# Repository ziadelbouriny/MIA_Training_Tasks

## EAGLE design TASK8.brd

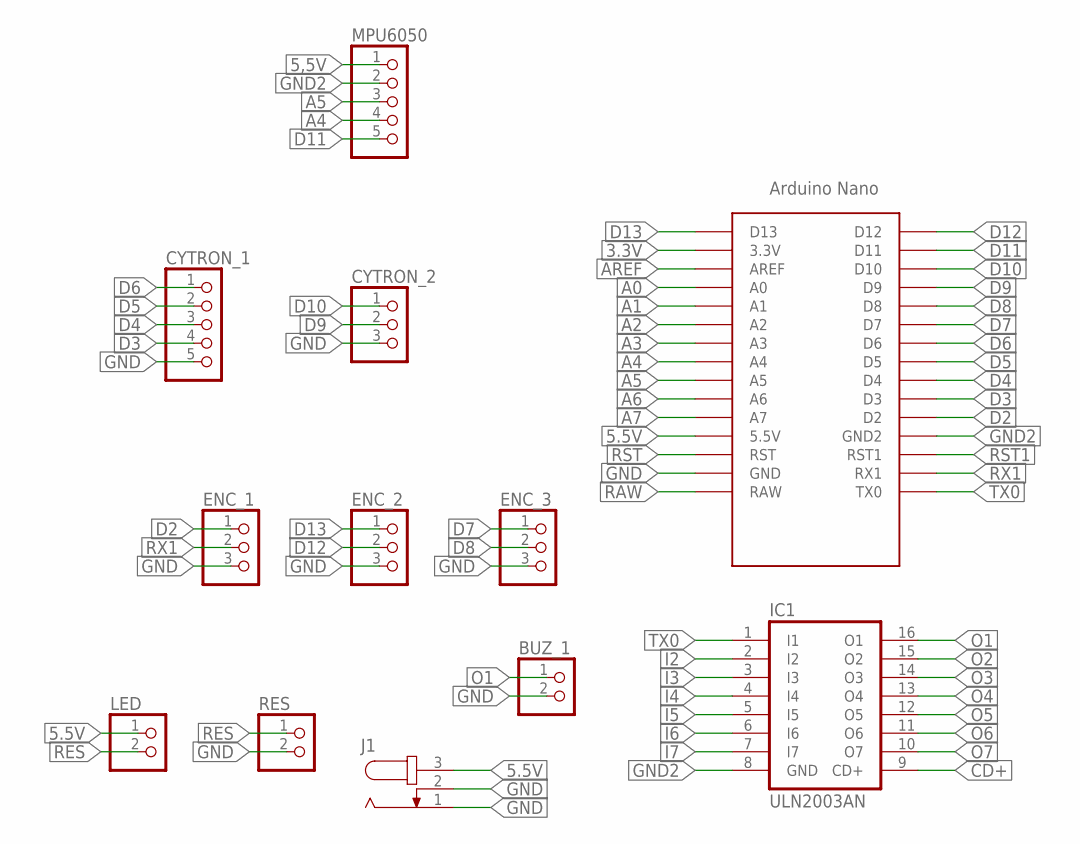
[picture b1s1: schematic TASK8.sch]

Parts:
BUZ_1: PINHD-1X2; 1X02
CYTRON_1: PINHD-1X5; 1X05
CYTRON_2: PINHD-1X3; 1X03
ENC_1, ENC_2, ENC_3: PINHD-1X3; 1X03
IC1: ULN2003AN; DIL16
J1: JACK-PLUG0; SPC4077
LED: PINHD-1X2; 1X02
MPU6050: PINHD-1X5; 1X05
RES: PINHD-1X2; 1X02
U$1: ARDUINO_NANO; NANO

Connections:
3.3V: U$1.3.3V
5,5V: MPU6050.1
5.5V: J1.3, LED.1, U$1.5V (5.5V)
A0: U$1.A0
A1: U$1.A1
A2: U$1.A2
A3: U$1.A3
A4: MPU6050.4, U$1.A4
A5: MPU6050.3, U$1.A5
A6: U$1.A6
A7: U$1.A7
AREF: U$1.AREF
CD+: IC1.9 (CD+)
D2: ENC_1.1, U$1.D2
D3: CYTRON_1.4, U$1.D3
D4: CYTRON_1.3, U$1.D4
D5: CYTRON_1.2, U$1.D5
D6: CYTRON_1.1, U$1.D6
D7: ENC_3.1, U$1.D7
D8: ENC_3.2, U$1.D8
D9: CYTRON_2.2, U$1.D9
D10: CYTRON_2.1, U$1.D10
D11: MPU6050.5, U$1.D11
D12: ENC_2.2, U$1.D12
D13: ENC_2.1, U$1.D13
GND: BUZ_1.2, CYTRON_1.5, CYTRON_2.3, ENC_1.3, ENC_2.3, ENC_3.3, J1.1, J1.2, RES.2, U$1.GND
GND2: IC1.8 (GND), MPU6050.2, U$1.GND1 (GND2)
I2: IC1.2 (I2)
I3: IC1.3 (I3)
I4: IC1.4 (I4)
I5: IC1.5 (I5)
I6: IC1.6 (I6)
I7: IC1.7 (I7)
O1: BUZ_1.1, IC1.16 (O1)
O2: IC1.15 (O2)
O3: IC1.14 (O3)
O4: IC1.13 (O4)
O5: IC1.12 (O5)
O6: IC1.11 (O6)
O7: IC1.10 (O7)
RAW: U$1.RAW
RES: LED.2, RES.1
RST: U$1.RST
RST1: U$1.RST1
RX1: ENC_1.2, U$1.RX1
TX0: IC1.1 (I1), U$1.TX0

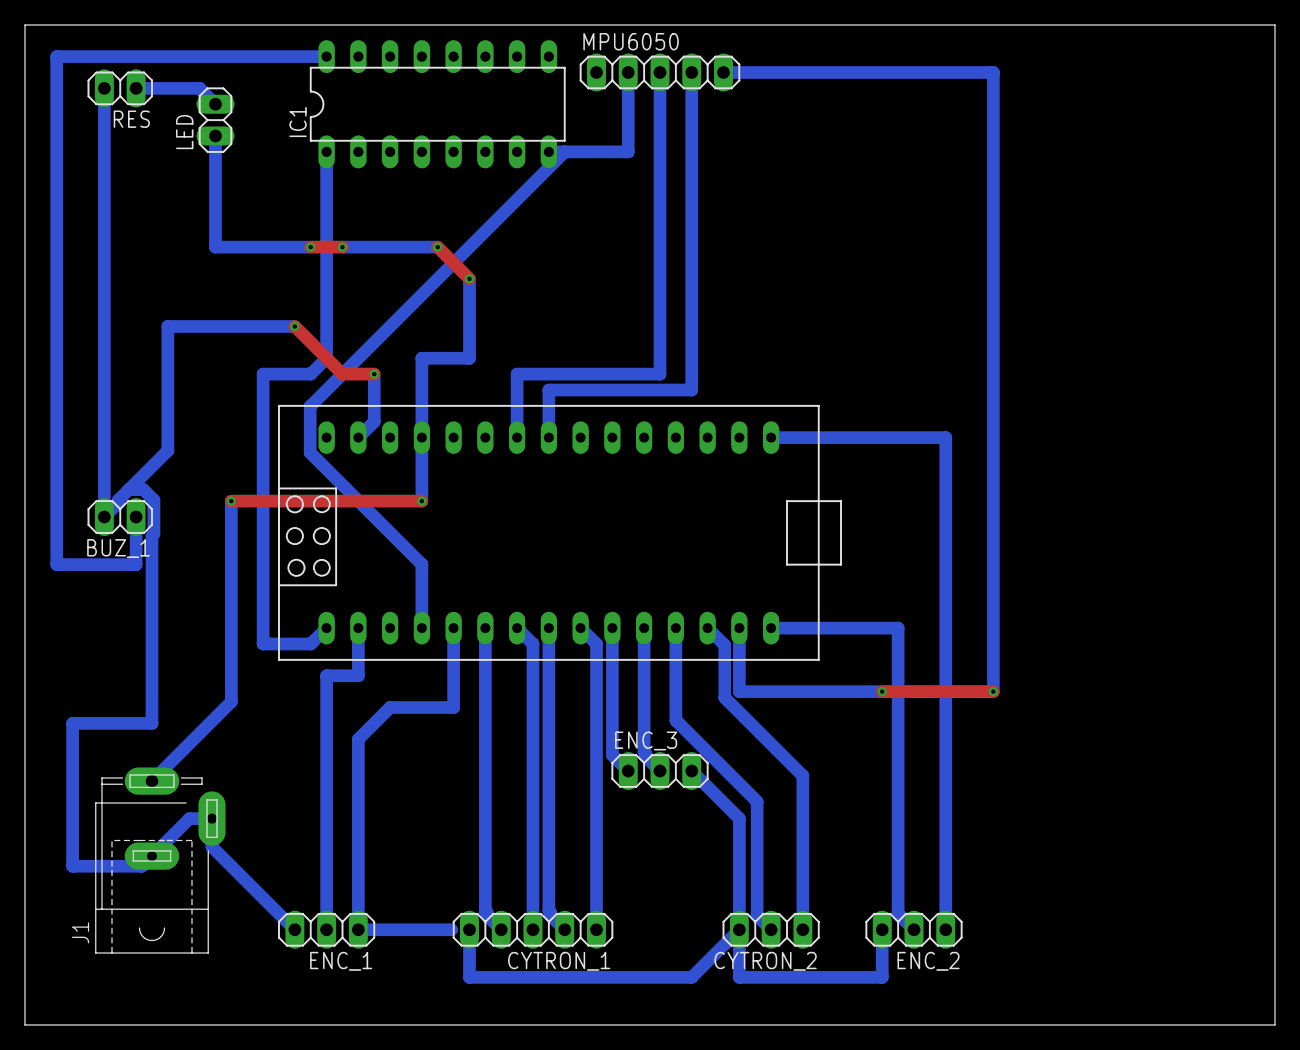
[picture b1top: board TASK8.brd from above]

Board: 2 copper layers, 100.0 x 80.0 mm, 12 parts (0 on the bottom side), 21 nets.

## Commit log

2022-08-11 Revert "Add files via upload"
    This reverts commit 3d7b824918d0d38e0dd5f4d70a5d4e216db8b0c6.
2022-08-11 Revert "Add files via upload"
    This reverts commit dde163e6757da2a994e64cff1868caae4aca34b5.
2022-08-11 Revert "Add files via upload"
    This reverts commit 0b4f4bcac04a0195102dbf5252e20f39080edc55.
2022-08-11 Revert "Add files via upload"
    This reverts commit 156f43235f96759386936fd751d64f8df95e5248.
2022-08-11 Revert "Add files via upload"
    This reverts commit 3290855c5ea9991f65f1e85b6ff0ea1478ef2fd9.
2022-08-12 Revert "Revert "Add files via upload""
    This reverts commit 213a9927276981e70bde6f5da4817cbdc89f8ff1.
2022-08-12 Revert "Revert "Add files via upload""
    This reverts commit 2f480eee24b09936b133336f3e409168305077f4.
2022-08-12 Revert "Revert "Add files via upload""
    This reverts commit 3de43a86150c22d3a69eefcfeb9c7720e42a2242.
2022-08-12 Revert "Revert "Add files via upload""
    This reverts commit 91dc6c9aa1de1f146c7a728dfa23293ba2b561a5.
2022-08-23 Revert "Revert "Revert "Add files via upload"""
    This reverts commit a78530ed967396ffaa695eb3f69af99f089514a1.
2022-08-23 Revert "Revert "Revert "Add files via upload"""
    This reverts commit 0431ec611de6652dac66b3e9a350b79c174714b4.
2022-08-23 Revert "Revert "Revert "Add files via upload"""
    This reverts commit 10128af69626f4e2a4747a19c77bdde7a6b8ed97.
2022-08-23 Revert "Revert "Revert "Add files via upload"""
    This reverts commit 7ae7b03b645bc4031fdf7c48bf586cc9a4cda1f8.
2022-08-23 Revert "Revert "Revert "Revert "Add files via upload""""
    This reverts commit 4efefbddbb75b093e16d09fb76e38a2e77d7d58f.
2022-08-23 Revert "Revert "Revert "Revert "Add files via upload""""
    This reverts commit 08e34b11fe1bc88b3e9c3e93e76936cdf498056c.
2022-08-23 Revert "Revert "Revert "Revert "Add files via upload""""
    This reverts commit 74e95a6e0355dbcce8384493bf99245d69048916.
2022-08-23 Revert "Revert "Revert "Revert "Add files via upload""""
    This reverts commit 054bbffbdf1556a8e2f7e1494ea1d1797c1aa0dd.
2022-08-23 linux_task
2022-08-23 Revert "Revert "Revert "Revert "Revert "Add files via upload"""""
    This reverts commit 59bcf9408d20f43705008233260ce126f7f31cd7.
2022-08-23 Revert "Revert "Revert "Revert "Revert "Add files via upload"""""
    This reverts commit 55362dac497aa2355af1228cc3339a69388d5bba.
2022-08-23 Revert "Revert "Revert "Revert "Revert "Add files via upload"""""
    This reverts commit 0d2f5f4b2f6a57b075603c09736d8d66885d1caa.
2022-08-23 Revert "Revert "Revert "Revert "Revert "Add files via upload"""""
    This reverts commit aa57b3a94ca929032fc72fae7eac13f38741c3eb.
2022-08-23 sequential image processing task
2022-08-23 Revert "linux_task"
    This reverts commit 29632f43adbe76bf33bd9442313d74c57edc2027.
2022-08-23 OOP image processing task
2022-08-23 Revert "sequential image processing task"
    This reverts commit e5aed7f2903f4c8391cae6b16fe9c15ade5737ea.
2022-08-31 Task 4
2022-08-31 Revert "OOP image processing task"
    This reverts commit 5c89c339829dbeb2976a26232dd4f28fb62c07fd.
2022-09-02 Task 6
2022-09-02 Revert "Task 4"
    This reverts commit f330eb9e1354d949b08f918a3cff797d168dfa93.
2022-09-03 Modification on Task6
2022-09-07 Task 8
2022-09-07 Revert "Task 6"
    This reverts commit ea96afec6744fcec806c02c3242ba9526fb7cc5d.
2022-09-07 Revert "Modification on Task6"
    This reverts commit 247e017c3aac86b28e4c19284ae97129033bda8e.
